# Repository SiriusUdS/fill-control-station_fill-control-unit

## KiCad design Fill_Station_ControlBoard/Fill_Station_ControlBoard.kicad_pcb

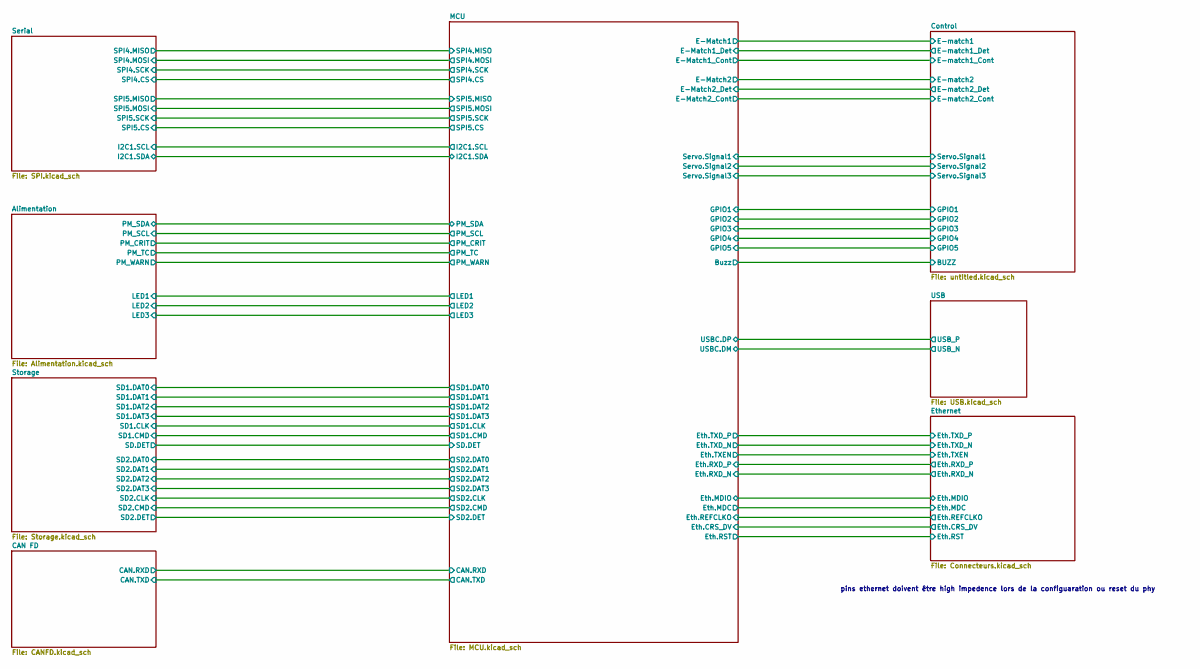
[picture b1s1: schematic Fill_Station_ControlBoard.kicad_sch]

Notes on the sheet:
pins ethernet doivent être high impedence lors de la configuaration ou reset du phy

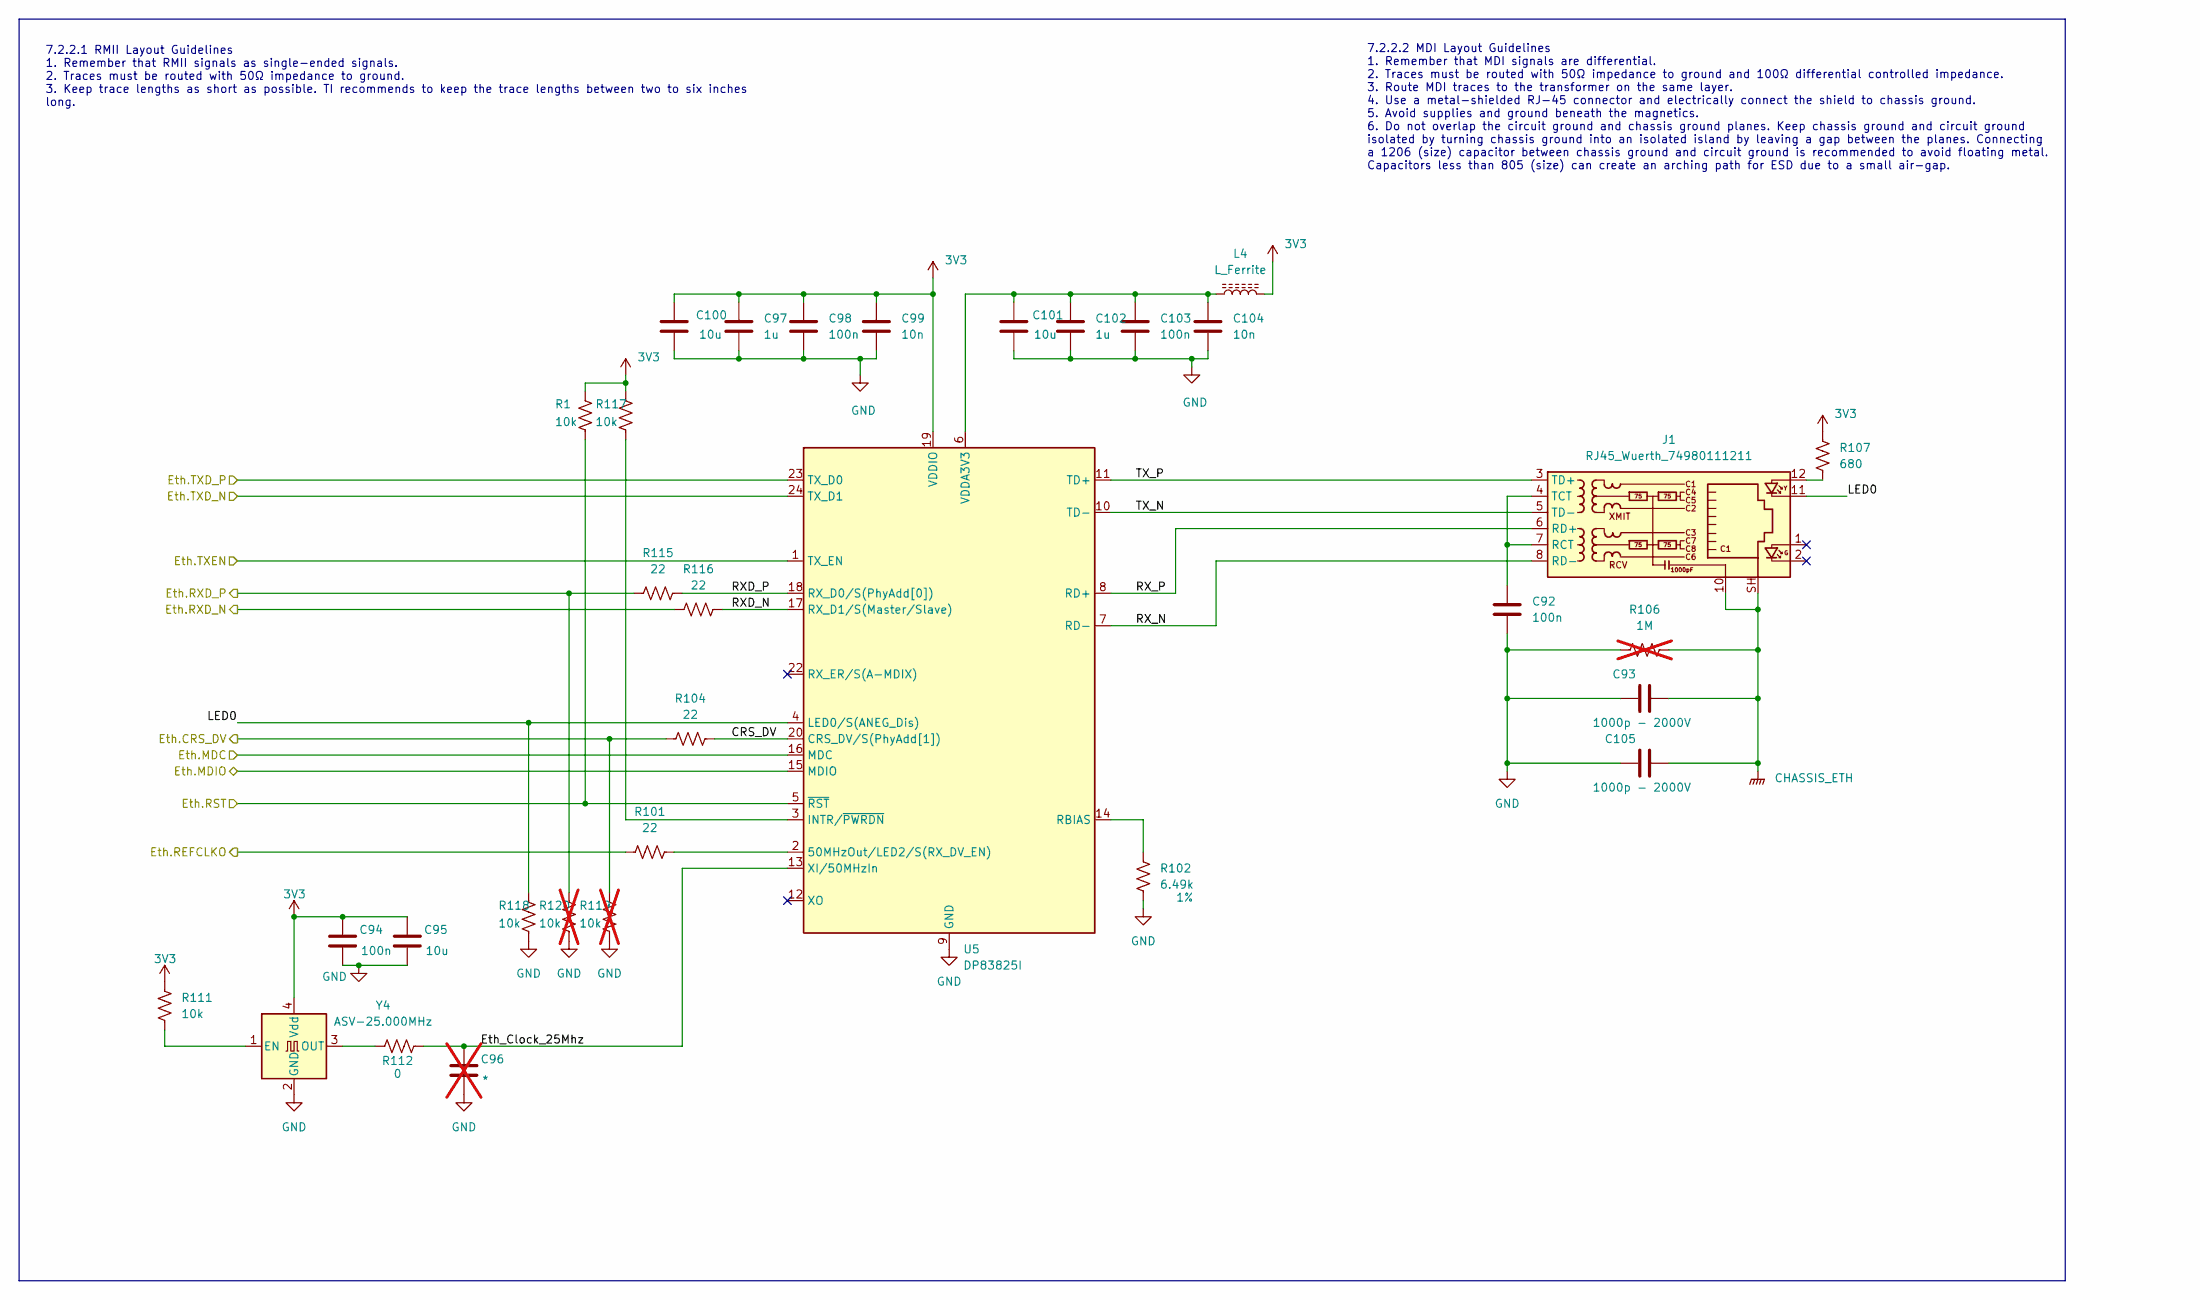
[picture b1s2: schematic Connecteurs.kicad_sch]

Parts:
C92, C94, C98, C103: 100n; C_0402_1005Metric; LCSC C60474
C93, C105: 1000p - 2000V; C_1210_3225Metric; LCSC C9196
C95, C100, C101: 10u; C_0603_1608Metric; LCSC C22399626
C96: *; C_0402_1005Metric; not fitted
C97, C102: 1u; C_0603_1608Metric; LCSC C59302
C99, C104: 10n; C_0402_1005Metric; LCSC C3850633
J1: RJ45_Wuerth_74980111211; RJ45_Wuerth_74980111211_Horizontal; LCSC C5523973
L4: L_Ferrite; R_0402_1005Metric; LCSC C160977
R1, R117, R118: 10k; R_0603_1608Metric; LCSC C22369937
R101, R104, R115, R116: 22; R_0402_1005Metric; LCSC C25092
R102: 6.49k; R_0402_1005Metric; LCSC C25916
R106: 1M; R_0603_1608Metric_Pad0.98x0.95mm_HandSolder; not fitted
R107: 680; R_0603_1608Metric_Pad0.98x0.95mm_HandSolder; LCSC C22356475
R111: 10k; R_0402_1005Metric; LCSC C173683
R112: 0; R_0402_1005Metric; LCSC C17168
R119, R120: 10k; R_0603_1608Metric; not fitted
U5: DP83825I; Texas_RMQ0024A_WQFN-24-1EP_3x3mm_P0.4mm_EP1.9x1.9mm; LCSC C783599
Y4: ASV-25.000MHz; Oscillator_SMD_Abracon_ASV-4Pin_7.0x5.1mm; LCSC C1987509

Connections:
3V3: C94.1, C95.1, C97.1, C98.1, C99.1, C100.1, L4.2, R1.1, R107.1, R111.1, R117.1, U5.19 (VDDIO), Y4.4 (Vdd); also elsewhere on the board
/Ethernet/CRS_DV: R104.2, U5.20 (CRS_DV/S(PhyAdd[1]))
/Ethernet/Eth.CRS_DV: R104.1, R119.1; also elsewhere on the board
/Ethernet/Eth.MDC: U5.16 (MDC); also elsewhere on the board
/Ethernet/Eth.MDIO: U5.15 (MDIO); also elsewhere on the board
/Ethernet/Eth.REFCLKO: R101.1; also elsewhere on the board
/Ethernet/Eth.RST: R1.2, U5.5 (~RST); also elsewhere on the board
/Ethernet/Eth.RXD_N: R116.1; also elsewhere on the board
/Ethernet/Eth.RXD_P: R115.1, R120.1; also elsewhere on the board
/Ethernet/Eth.TXD_N: U5.24 (TX_D1); also elsewhere on the board
/Ethernet/Eth.TXD_P: U5.23 (TX_D0); also elsewhere on the board
/Ethernet/Eth.TXEN: U5.1 (TX_EN); also elsewhere on the board
/Ethernet/Eth_Clock_25Mhz: C96.1, R112.2, U5.13 (XI/50MHzIn)
/Ethernet/LED0: J1.11, R118.1, U5.4 (LED0/S(ANEG_Dis))
/Ethernet/RXD_N: R116.2, U5.17 (RX_D1/S(Master/Slave))
/Ethernet/RXD_P: R115.2, U5.18 (RX_D0/S(PhyAdd[0]))
/Ethernet/RX_N: J1.8 (RD-), U5.7 (RD-)
/Ethernet/RX_P: J1.6 (RD+), U5.8 (RD+)
/Ethernet/TX_N: J1.5 (TD-), U5.10 (TD-)
/Ethernet/TX_P: J1.3 (TD+), U5.11 (TD+)
CHASSIS_ETH: C93.2, C105.2, J1.10, J1.SH, R106.2
GND: C92.2, C93.1, C94.2, C95.2, C96.2, C97.2, C98.2, C99.2, C100.2, C101.2, C102.2, C103.2, C104.2, C105.1, R102.2, R106.1, R118.2, R119.2, R120.2, U5.9 (GND), U5.21 (GND), U5.25 (GND), Y4.2 (GND); also elsewhere on the board
unnamed: J1.12, R107.2
unnamed: C92.1, J1.4 (TCT), J1.7 (RCT)
unnamed: R101.2, U5.2 (50MHzOut/LED2/S(RX_DV_EN))
unnamed: R117.2, U5.3 (INTR/~PWRDN)
unnamed: R102.1, U5.14 (RBIAS)
unnamed: C101.1, C102.1, C103.1, C104.1, L4.1, U5.6 (VDDA3V3)
unnamed: R111.2, Y4.1 (EN)
unnamed: R112.1, Y4.3 (OUT)

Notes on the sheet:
7.2.2.1 RMII Layout Guidelines 1. Remember that RMII signals as single-ended signals. 2. Traces must be routed with 50Ω impedance to ground. 3. Keep trace lengths as short as possible. TI recommends to keep the trace lengths between two to six inches long.
7.2.2.2 MDI Layout Guidelines 1. Remember that MDI signals are differential. 2. Traces must be routed with 50Ω impedance to ground and 100Ω differential controlled impedance. 3. Route MDI traces to the transformer on the same layer. 4. Use a metal-shielded RJ-45 connector and electrically connect t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

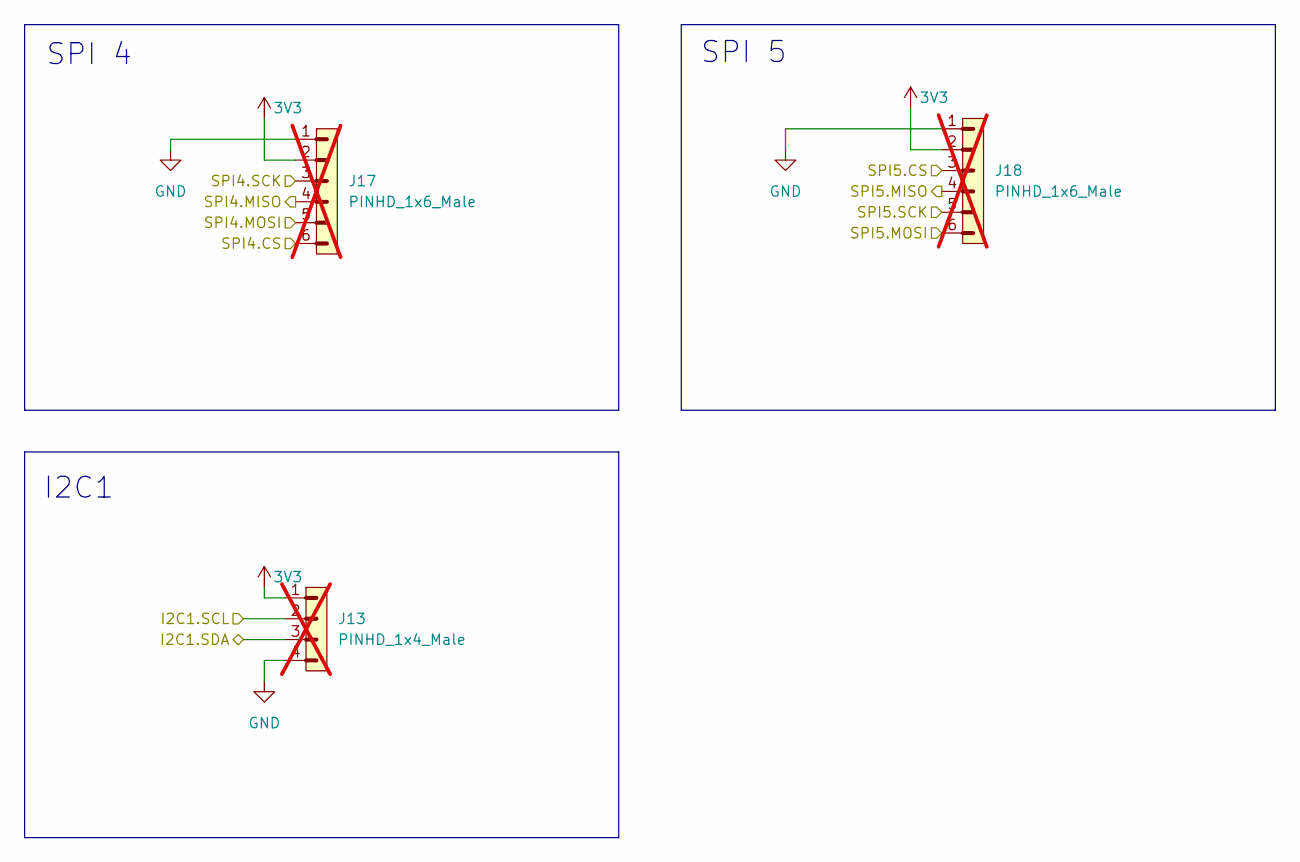
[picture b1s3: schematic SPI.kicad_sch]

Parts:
J13: PINHD_1x4_Male; PinHeader_1x04_P2.54mm_Vertical; not fitted
J17, J18: PINHD_1x6_Male; PinHeader_1x06_P2.54mm_Vertical; not fitted

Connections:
3V3: J13.1, J17.2, J18.2; also elsewhere on the board
/MCU/I2C1.SCL: J13.2; also elsewhere on the board
/MCU/I2C1.SDA: J13.3; also elsewhere on the board
/MCU/SPI4.CS: J17.6; also elsewhere on the board
/MCU/SPI4.MISO: J17.4; also elsewhere on the board
/MCU/SPI4.MOSI: J17.5; also elsewhere on the board
/MCU/SPI4.SCK: J17.3; also elsewhere on the board
/MCU/SPI5.CS: J18.3; also elsewhere on the board
/MCU/SPI5.MISO: J18.4; also elsewhere on the board
/MCU/SPI5.MOSI: J18.6; also elsewhere on the board
/MCU/SPI5.SCK: J18.5; also elsewhere on the board
GND: J13.4, J17.1, J18.1; also elsewhere on the board

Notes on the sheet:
SPI 5
SPI 4
I2C1

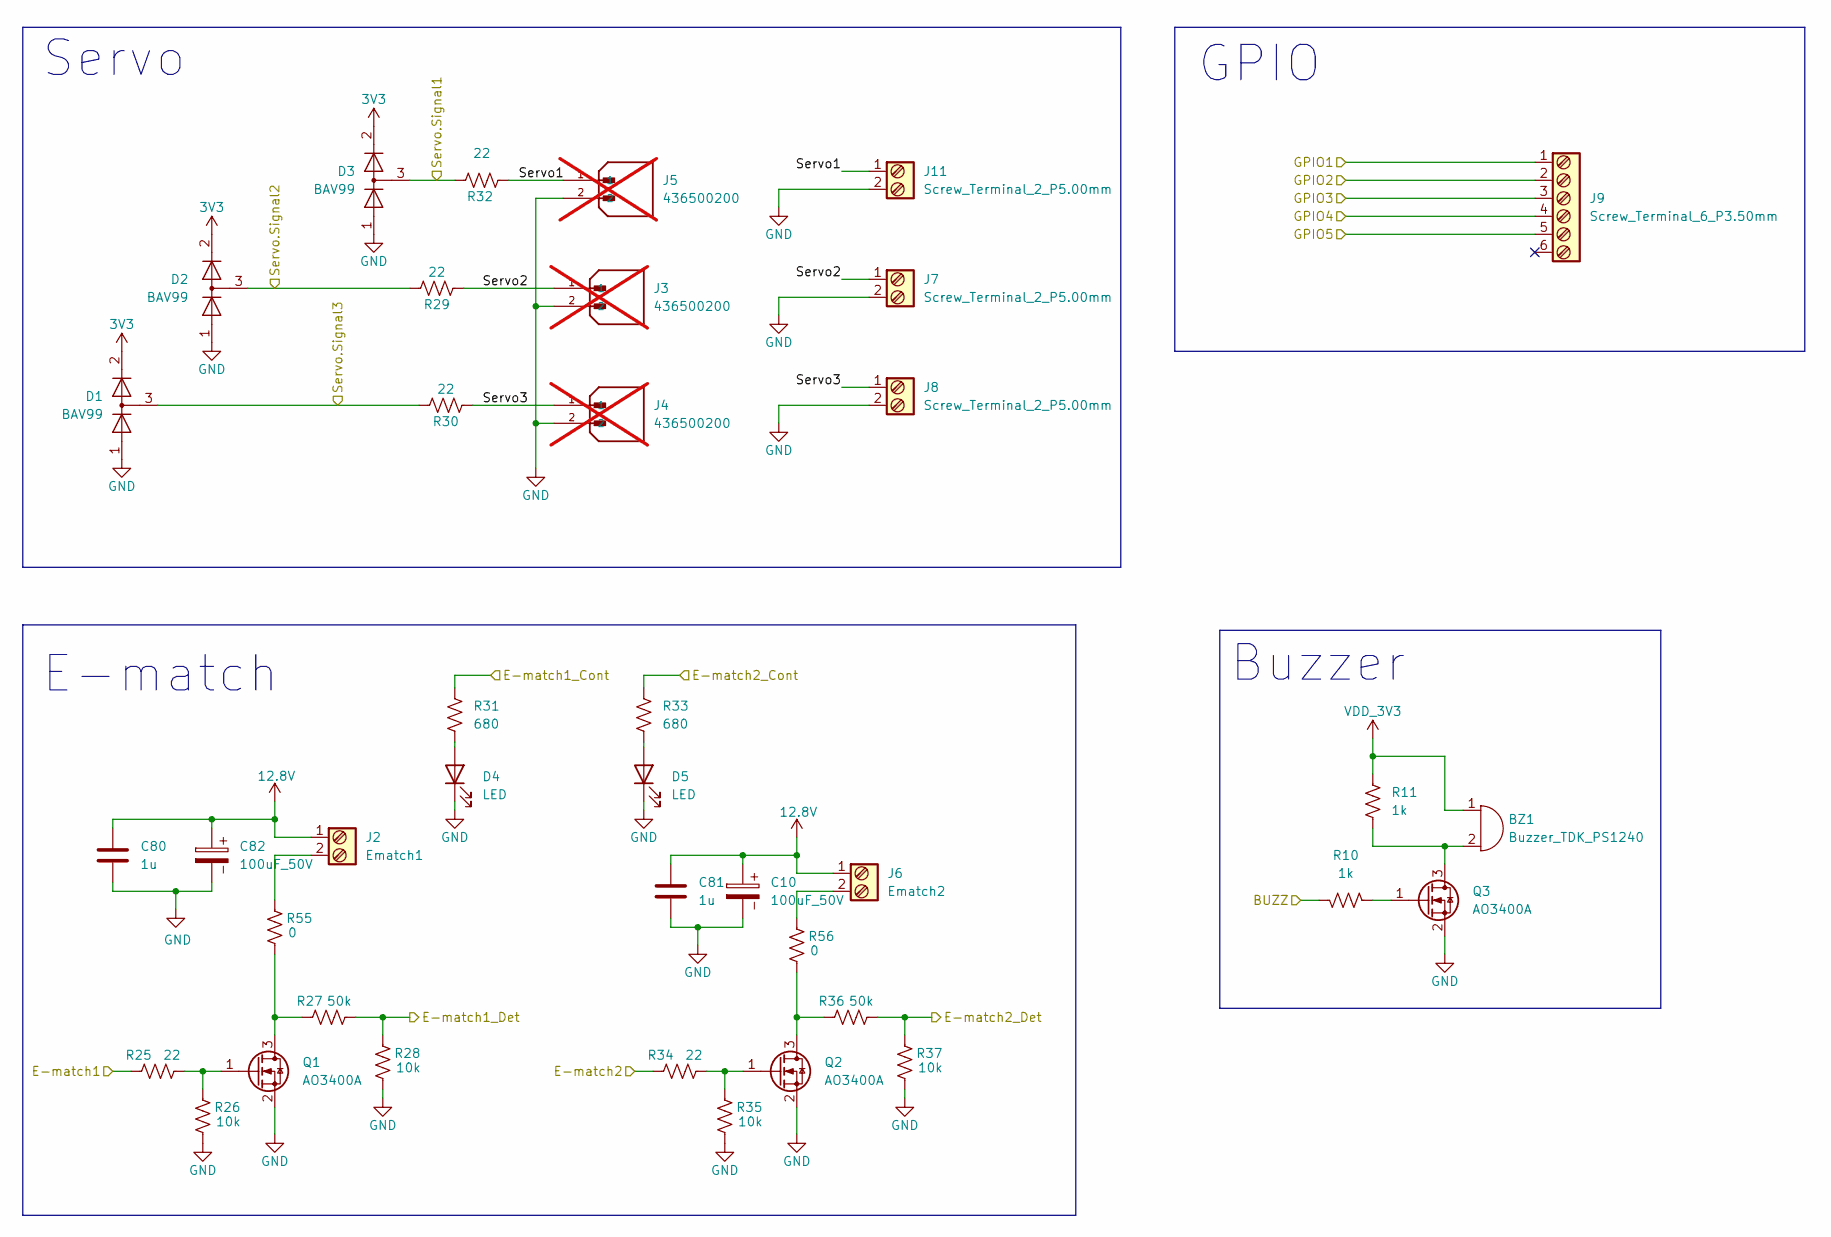
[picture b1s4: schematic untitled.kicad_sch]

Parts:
BZ1: Buzzer_TDK_PS1240; Buzzer_Murata_PKMCS0909E; Manufacturer Part Number PS1240P02BT; LCSC C910763
C10, C82: 100uF_50V; CP_Elec_6.3x7.7; LCSC C165974
C80, C81: 1u; C_0603_1608Metric; LCSC C59302
D1, D2, D3: BAV99; SOT-23; LCSC C68983
D4, D5: LED; LED_0603_1608Metric; LCSC C2286
J2: Ematch1; TerminalBlock_Phoenix_PT-1,5-2-5.0-H_1x02_P5.00mm_Horizontal
J3, J4, J5: 436500200; MOLEX_436500200; PARTREV D7; not fitted
J6: Ematch2; TerminalBlock_Phoenix_PT-1,5-2-5.0-H_1x02_P5.00mm_Horizontal
J7, J8, J11: Screw_Terminal_2_P5.00mm; TerminalBlock_Phoenix_PT-1,5-2-5.0-H_1x02_P5.00mm_Horizontal
J9: Screw_Terminal_6_P3.50mm; TerminalBlock_Phoenix_PT-1,5-6-3.5-H_1x06_P3.50mm_Horizontal
Q1, Q2, Q3: AO3400A; SOT-23; LCSC C20917
R10, R11: 1k; R_0603_1608Metric; LCSC C22356624
R25, R29, R30, R32, R34: 22; R_0402_1005Metric; LCSC C25092
R26, R28, R35, R37: 10k; R_0603_1608Metric; LCSC C22369937
R27, R36: 50k; R_0603_1608Metric_Pad0.98x0.95mm_HandSolder; LCSC C861451
R31, R33: 680; R_0603_1608Metric_Pad0.98x0.95mm_HandSolder; LCSC C22356475
R55, R56: 0; R_0402_1005Metric; LCSC C17168

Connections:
3V3: D1.2 (A), D2.2 (A), D3.2 (A); also elsewhere on the board
12.8V: C10.1, C80.1, C81.1, C82.1, J2.1, J6.1; also elsewhere on the board
/Control/BUZZ: R10.2; also elsewhere on the board
/Control/E-match1: R25.1; also elsewhere on the board
/Control/E-match1_Cont: R31.2; also elsewhere on the board
/Control/E-match1_Det: R27.2, R28.1; also elsewhere on the board
/Control/E-match2: R34.1; also elsewhere on the board
/Control/E-match2_Cont: R33.2; also elsewhere on the board
/Control/E-match2_Det: R36.2, R37.1; also elsewhere on the board
/Control/GPIO1: J9.1; also elsewhere on the board
/Control/GPIO2: J9.2; also elsewhere on the board
/Control/GPIO3: J9.3; also elsewhere on the board
/Control/GPIO4: J9.4; also elsewhere on the board
/Control/GPIO5: J9.5; also elsewhere on the board
/Control/Servo1: J5.1, J11.1, R32.2
/Control/Servo2: J3.1, J7.1, R29.1
/Control/Servo3: J4.1, J8.1, R30.1
/Control/Servo.Signal1: D3.3 (K), R32.1; also elsewhere on the board
/Control/Servo.Signal2: D2.3 (K), R29.2; also elsewhere on the board
/Control/Servo.Signal3: D1.3 (K), R30.2; also elsewhere on the board
GND: C10.2, C80.2, C81.2, C82.2, D1.1 (K), D2.1 (K), D3.1 (K), D4.1 (K), D5.1 (K), J3.2, J4.2, J5.2, J7.2, J8.2, J11.2, Q1.2 (S), Q2.2 (S), Q3.2 (S), R26.2, R28.2, R35.2, R37.2; also elsewhere on the board
unnamed: D4.2 (A), R31.1
unnamed: D5.2 (A), R33.1
unnamed: J2.2, R55.1
unnamed: J6.2, R56.1
unnamed: Q1.3 (D), R27.1, R55.2
unnamed: Q1.1 (G), R25.2, R26.1
unnamed: Q2.3 (D), R36.1, R56.2
unnamed: Q2.1 (G), R34.2, R35.1
unnamed: BZ1.2, Q3.3 (D), R11.2
unnamed: Q3.1 (G), R10.1
VDD_3V3: BZ1.1, R11.1

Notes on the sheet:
GPIO
E-match
Buzzer
Servo

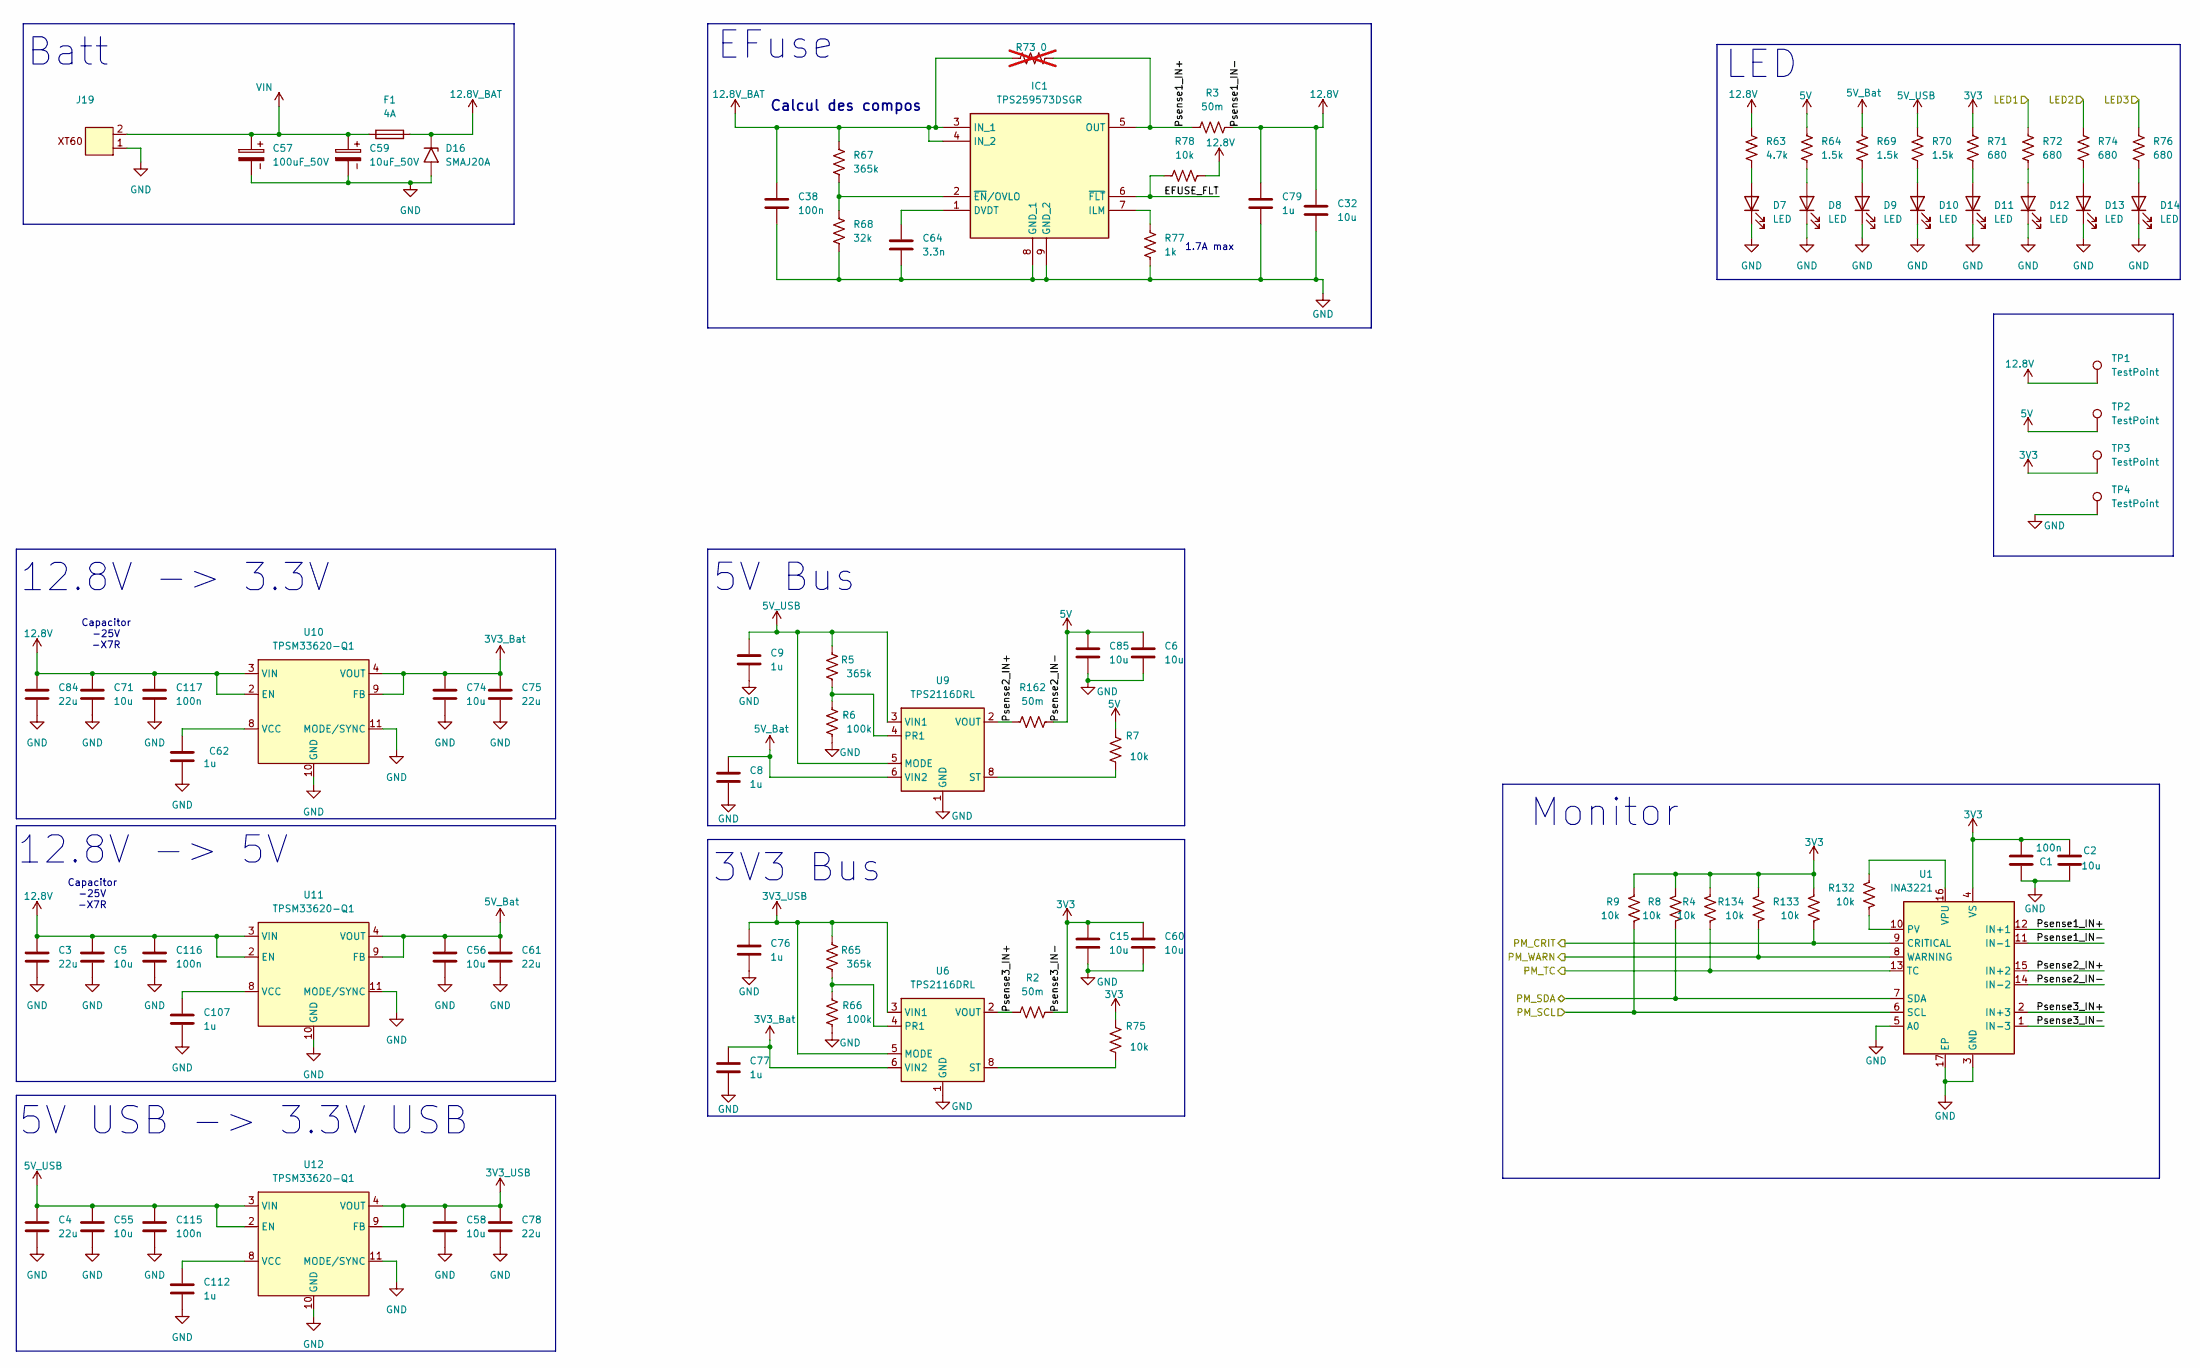
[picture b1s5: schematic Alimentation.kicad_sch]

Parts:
C1, C38, C115, C116, C117: 100n; C_0603_1608Metric; LCSC C14663
C2, C6, C15, C56, C58, C60, C74, C85: 10u; C_0603_1608Metric; LCSC C22399626
C3, C4: 22u; C_1210_3225Metric; LCSC C5341638
C5, C55, C71: 10u; C_0805_2012Metric; LCSC C326595
C8, C9, C62, C76, C77, C79, C107, C112: 1u; C_0603_1608Metric; LCSC C59302
C32: 10u; C_0603_1608Metric
C57: 100uF_50V; CP_Elec_6.3x7.7; LCSC C165974
C59: 10uF_50V; CP_Elec_5x5.3
C61, C75, C78: 22u; C_0603_1608Metric; LCSC C60077
C64: 3.3n; C_0603_1608Metric
C84: 22u; R_0603_1608Metric; LCSC C5341638
D7, D11, D12: LED; LED_0603_1608Metric; LCSC C12065
D8, D9, D10: LED; LED_0603_1608Metric; LCSC C2288
D13, D14: LED; LED_0603_1608Metric; LCSC C2286
D16: SMAJ20A; D_SMA; LCSC C10763
F1: 4A; Fuse_0603_1608Metric; LCSC C187606
IC1: TPS259573DSGR; WSON-8-1EP_2x2mm_P0.5mm_EP0.9x1.6mm_ThermalVias; Mouser Part Number 595-TPS259573DSGR
J19: AMASS_XT60-M_1x02_P7.20mm_Vertical; LCSC C98733
R2, R3, R162: 50m; R_0603_1608Metric; LCSC C2074926
R4, R8, R9, R132, R133, R134: 10k; R_0402_1005Metric; LCSC C173683
R5, R65, R67: 365k; R_0603_1608Metric
R6: 100k; R_0603_1608Metric
R7: 10k; C_0603_1608Metric; LCSC C22369937
R63: 4.7k; C_0603_1608Metric
R64, R69, R70: 1.5k; R_0603_1608Metric_Pad0.98x0.95mm_HandSolder
R66: 100k; C_0603_1608Metric
R68: 32k; R_0603_1608Metric
R71, R72, R74, R76: 680; R_0603_1608Metric_Pad0.98x0.95mm_HandSolder; LCSC C22356475
R73: 0; R_0402_1005Metric; not fitted
R75, R78: 10k; R_0603_1608Metric; LCSC C22369937
R77: 1k; R_0603_1608Metric; LCSC C22356624
TP1, TP2, TP3, TP4: TestPoint; TestPoint_Pad_D2.0mm
U1: INA3221; Texas_RGV0016A_VQFN-16-1EP_4x4mm_P0.65mm_EP2.1x2.1mm; LCSC C181255
U6, U9: TPS2116DRL; SOT-583-8; LCSC C3235557
U10, U12: TPSM33620-Q1; RDN0011A-MFG; LCSC C49261907
U11: TPSM33620-Q1; RDN0011A-MFG; LCSC C51956999

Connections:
3V3: C1.1, C2.2, C15.1, C60.1, R2.2, R4.1, R8.1, R9.1, R71.2, R75.2, R133.1, R134.1, TP3.1, U1.1 (IN-3), U1.4 (VS); also elsewhere on the board
3V3_Bat: C74.1, C75.1, C77.1, U6.6 (VIN2), U10.4 (VOUT), U10.9 (FB)
3V3_USB: C58.1, C76.1, C78.1, R65.2, U6.3 (VIN1), U6.5 (MODE), U12.4 (VOUT), U12.9 (FB)
5V: C6.1, C85.1, R7.2, R64.2, R162.2, TP2.1, U1.14 (IN-2); also elsewhere on the board
5V_Bat: C8.1, C56.1, C61.1, R69.2, U9.6 (VIN2), U11.4 (VOUT), U11.9 (FB)
5V_USB: C4.1, C9.1, C55.1, C115.1, R5.2, R70.2, U9.3 (VIN1), U9.5 (MODE), U12.2 (EN), U12.3 (VIN); also elsewhere on the board
12.8V: C3.1, C5.1, C32.1, C71.1, C79.1, C84.1, C116.1, C117.1, R3.2, R63.2, R78.2, TP1.1, U1.11 (IN-1), U10.2 (EN), U10.3 (VIN), U11.2 (EN), U11.3 (VIN); also elsewhere on the board
12.8V_BAT: C38.1, D16.1 (A1), F1.2, IC1.3 (IN_1), IC1.4 (IN_2), R67.1, R73.1
/Alimentation/EFUSE_FLT: IC1.6 (~FLT), R78.1
/Alimentation/LED1: R72.2; also elsewhere on the board
/Alimentation/LED2: R74.2; also elsewhere on the board
/Alimentation/LED3: R76.2; also elsewhere on the board
/Alimentation/PM_CRIT: R133.2, U1.9 (CRITICAL); also elsewhere on the board
/Alimentation/PM_SCL: R9.2, U1.6 (SCL); also elsewhere on the board
/Alimentation/PM_SDA: R8.2, U1.7 (SDA); also elsewhere on the board
/Alimentation/PM_TC: R4.2, U1.13 (TC); also elsewhere on the board
/Alimentation/PM_WARN: R134.2, U1.8 (WARNING); also elsewhere on the board
/Alimentation/Psense1_IN+: IC1.5 (OUT), R3.1, R73.2, U1.12 (IN+1)
/Alimentation/Psense2_IN+: R162.1, U1.15 (IN+2), U9.2 (VOUT), U9.7 (VOUT)
/Alimentation/Psense3_IN+: R2.1, U1.2 (IN+3), U6.2 (VOUT), U6.7 (VOUT)
GND: C1.2, C2.1, C3.2, C4.2, C5.2, C6.2, C8.2, C9.2, C15.2, C32.2, C38.2, C55.2, C56.2, C57.2, C58.2, C59.2, C60.2, C61.2, C62.2, C64.2, C71.2, C74.2, C75.2, C76.2, C77.2, C78.2, C79.2, C84.2, C85.2, C107.2, C112.2, C115.2, C116.2, C117.2, D7.1 (K), D8.1 (K), D9.1 (K), D10.1 (K), D11.1 (K), D12.1 (K), D13.1 (K), D14.1 (K), D16.2 (A2), IC1.8 (GND_1), IC1.9 (GND_2), J19.1, R6.1, R66.1, R68.2, R77.2, TP4.1, U1.3 (GND), U1.5 (A0), U1.17 (EP), U6.1 (GND), U9.1 (GND), U10.10 (GND), U10.11 (MODE/SYNC), U11.10 (GND), U11.11 (MODE/SYNC), U12.10 (GND), U12.11 (MODE/SYNC); also elsewhere on the board
unnamed: D7.2 (A), R63.1
unnamed: D8.2 (A), R64.1
unnamed: D9.2 (A), R69.1
unnamed: D10.2 (A), R70.1
unnamed: D11.2 (A), R71.1
unnamed: D12.2 (A), R72.1
unnamed: D13.2 (A), R74.1
unnamed: D14.2 (A), R76.1
unnamed: C64.1, IC1.1 (DVDT)
unnamed: IC1.7 (ILM), R77.1
unnamed: IC1.2 (~EN/OVLO), R67.2, R68.1
unnamed: R132.2, U1.10 (PV)
unnamed: R132.1, U1.16 (VPU)
unnamed: R65.1, R66.2, U6.4 (PR1)
unnamed: R75.1, U6.8 (ST)
unnamed: R5.1, R6.2, U9.4 (PR1)
unnamed: R7.1, U9.8 (ST)
unnamed: C62.1, U10.8 (VCC)
unnamed: C107.1, U11.8 (VCC)
unnamed: C112.1, U12.8 (VCC)
VIN: C57.1, C59.1, F1.1, J19.2

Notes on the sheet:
5V USB -> 3.3V USB
1.7A max
12.8V -> 3.3V
3V3 Bus
Capacitor -25V -X7R
12.8V -> 5V
Calcul des compos
EFuse
5V Bus
Batt
Monitor
LED

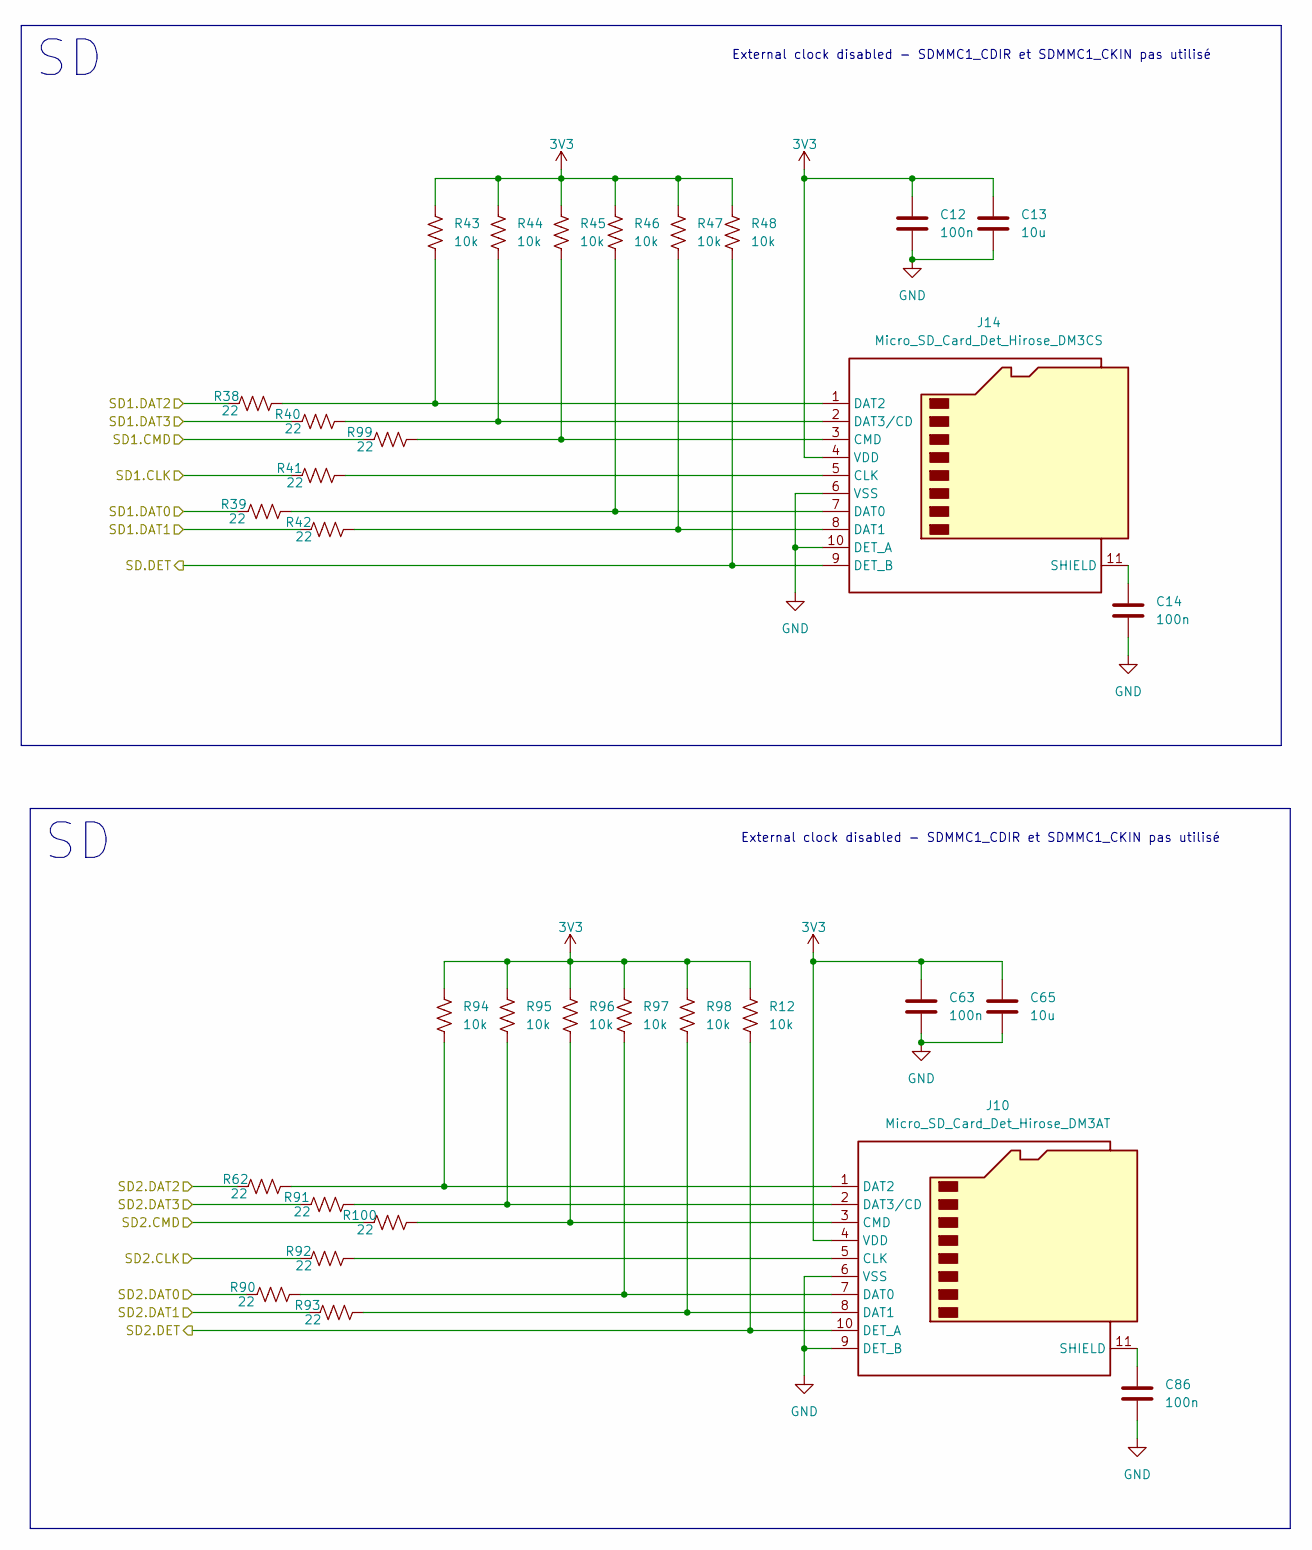
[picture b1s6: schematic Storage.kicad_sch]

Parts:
C12, C14, C63, C86: 100n; C_0603_1608Metric; LCSC C14663
C13, C65: 10u; C_0603_1608Metric; LCSC C22399626
J10: Micro_SD_Card_Det_Hirose_DM3AT; microSD_HC_Hirose_DM3AT-SF-PEJM5; LCSC C114218
J14: Micro_SD_Card_Det_Hirose_DM3CS; HRS_DM3CS-SF; LCSC C202111
R12, R43, R44, R45, R46, R47, R48, R94, R95, R96, R97, R98: 10k; R_0402_1005Metric; LCSC C173683
R38, R39, R40, R41, R42, R62, R90, R91, R92, R93, R99, R100: 22; R_0402_1005Metric; LCSC C25092

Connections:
3V3: C12.1, C13.1, C63.1, C65.1, J10.4 (VDD), J14.4 (VDD), R12.1, R43.1, R44.1, R45.1, R46.1, R47.1, R48.1, R94.1, R95.1, R96.1, R97.1, R98.1; also elsewhere on the board
/MCU/SD1.CLK: R41.1; also elsewhere on the board
/MCU/SD1.CMD: R99.1; also elsewhere on the board
/MCU/SD1.DAT0: R39.1; also elsewhere on the board
/MCU/SD1.DAT1: R42.1; also elsewhere on the board
/MCU/SD1.DAT2: R38.1; also elsewhere on the board
/MCU/SD1.DAT3: R40.1; also elsewhere on the board
/MCU/SD2.CLK: R92.1; also elsewhere on the board
/MCU/SD2.CMD: R100.1; also elsewhere on the board
/MCU/SD2.DAT0: R90.1; also elsewhere on the board
/MCU/SD2.DAT1: R93.1; also elsewhere on the board
/MCU/SD2.DAT2: R62.1; also elsewhere on the board
/MCU/SD2.DAT3: R91.1; also elsewhere on the board
/MCU/SD2.DET: J10.10 (DET_A), R12.2; also elsewhere on the board
/MCU/SD.DET: J14.9 (DET_B), R48.2; also elsewhere on the board
GND: C12.2, C13.2, C14.2, C63.2, C65.2, C86.2, J10.6 (VSS), J10.9 (DET_B), J14.6 (VSS), J14.10 (DET_A); also elsewhere on the board
unnamed: J10.5 (CLK), R92.2
unnamed: J10.3 (CMD), R96.2, R100.2
unnamed: J10.7 (DAT0), R90.2, R97.2
unnamed: J10.8 (DAT1), R93.2, R98.2
unnamed: J10.1 (DAT2), R62.2, R94.2
unnamed: J10.2 (DAT3/CD), R91.2, R95.2
unnamed: C86.1, J10.11 (SHIELD)
unnamed: J14.5 (CLK), R41.2
unnamed: J14.3 (CMD), R45.2, R99.2
unnamed: J14.7 (DAT0), R39.2, R46.2
unnamed: J14.8 (DAT1), R42.2, R47.2
unnamed: J14.1 (DAT2), R38.2, R43.2
unnamed: J14.2 (DAT3/CD), R40.2, R44.2
unnamed: C14.1, J14.11 (SHIELD)

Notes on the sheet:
External clock disabled - SDMMC1_CDIR et SDMMC1_CKIN pas utilisé

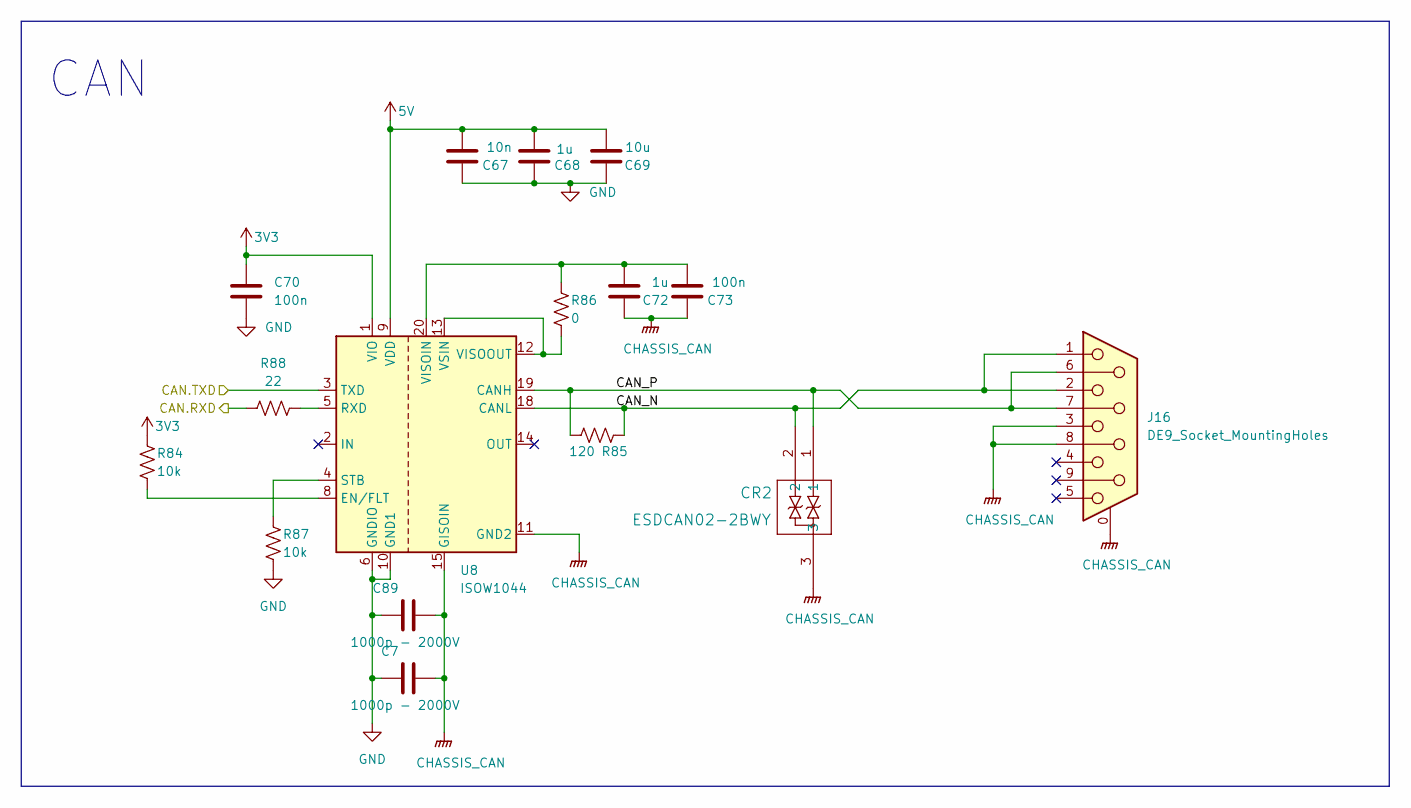
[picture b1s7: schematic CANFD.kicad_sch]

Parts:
C7, C89: 1000p - 2000V; C_1210_3225Metric; LCSC C9196
C67: 10n; C_0603_1608Metric; LCSC C100042
C68, C72: 1u; C_0603_1608Metric; LCSC C59302
C69: 10u; C_0603_1608Metric; LCSC C22399626
C70, C73: 100n; C_0603_1608Metric; LCSC C14663
CR2: ESDCAN02-2BWY; SOT323-3L_STM; LCSC C2969759
J16: DE9_Socket_MountingHoles; DSUB-9_Socket_Vertical_P2.77x2.84mm_MountingHoles; LCSC C141882
R84, R87: 10k; R_0603_1608Metric; LCSC C22369937
R85: 120; R_0603_1608Metric_Pad0.98x0.95mm_HandSolder; LCSC C177328
R86: 0; R_0402_1005Metric; LCSC C17168
R88: 22; R_0402_1005Metric; LCSC C25092
U8: ISOW1044; SOIC-20W_7.5x12.8mm_P1.27mm; LCSC C3234830

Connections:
3V3: C70.1, R84.1, U8.1 (VIO); also elsewhere on the board
5V: C67.2, C68.2, C69.2, U8.9 (VDD); also elsewhere on the board
/CAN FD/CAN.RXD: R88.1; also elsewhere on the board
/CAN FD/CAN.TXD: U8.3 (TXD); also elsewhere on the board
/CAN FD/CAN_N: CR2.2, J16.1, J16.2, R85.1, U8.18 (CANL)
/CAN FD/CAN_P: CR2.1, J16.6, J16.7, R85.2, U8.19 (CANH)
CHASSIS_CAN: C7.2, C72.1, C73.1, C89.2, CR2.3, J16.0 (PAD), J16.3, J16.8, U8.11 (GND2), U8.15 (GISOIN), U8.16 (GISOIN), U8.17 (GISOIN)
GND: C7.1, C67.1, C68.1, C69.1, C70.2, C89.1, R87.2, U8.6 (GNDIO), U8.10 (GND1); also elsewhere on the board
unnamed: R84.2, U8.8 (EN/FLT)
unnamed: R88.2, U8.5 (RXD)
unnamed: R87.1, U8.4 (STB)
unnamed: C72.2, C73.2, R86.1, U8.20 (VISOIN)
unnamed: R86.2, U8.12 (VISOOUT), U8.13 (VSIN)

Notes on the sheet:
CAN
